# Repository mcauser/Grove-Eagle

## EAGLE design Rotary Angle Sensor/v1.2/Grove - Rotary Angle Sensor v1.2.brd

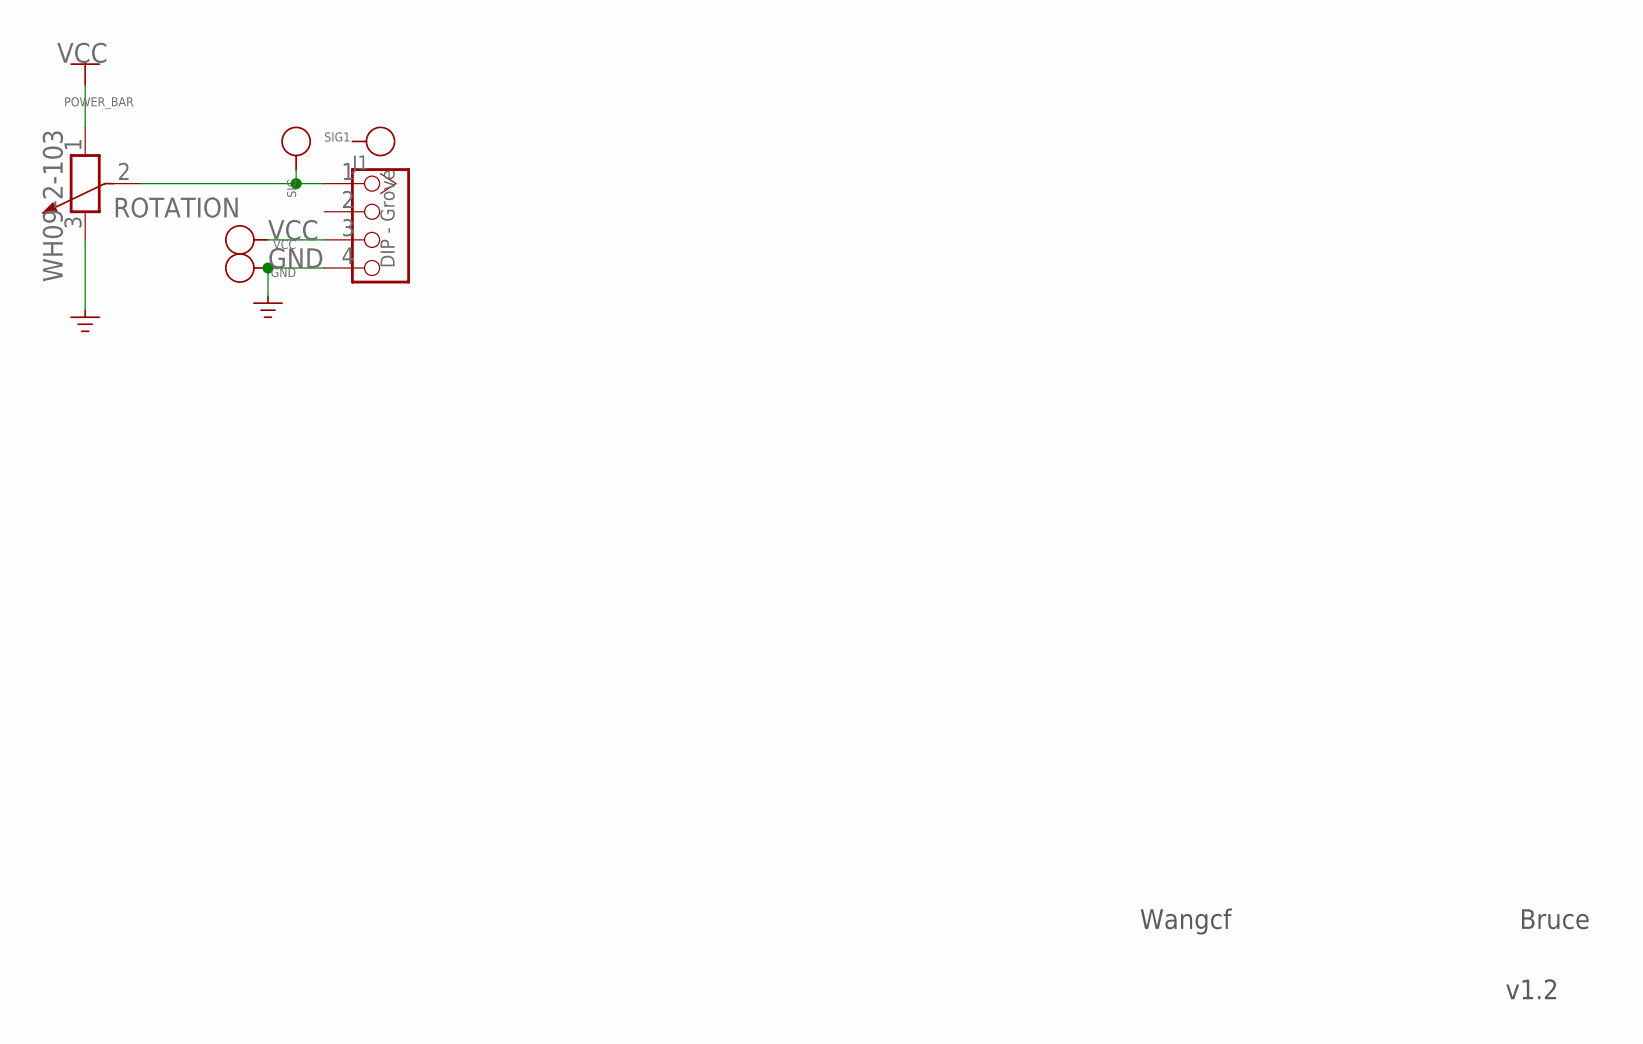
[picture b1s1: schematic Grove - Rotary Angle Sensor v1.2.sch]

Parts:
GND: PAD-TEST-POINT'4545'; TP_4545
J1: DIP - Grove; 4P-2.0
ROTATION: WH09-2-103; 3P-SQUA-11X9.8X12H
SIG, SIG1: PAD-TEST-POINT'4545'; TP_4545
VCC: PAD-TEST-POINT'4545'; TP_4545

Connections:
GND: GND.T, J1.4, ROTATION.3 (2)
unnamed: J1.1, ROTATION.2 (3), SIG.T
VCC: J1.3, ROTATION.1, VCC.T

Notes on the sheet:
Wangcf
Bruce
v1.2

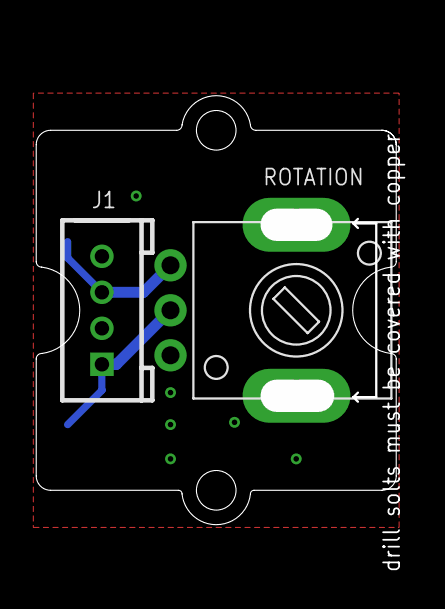
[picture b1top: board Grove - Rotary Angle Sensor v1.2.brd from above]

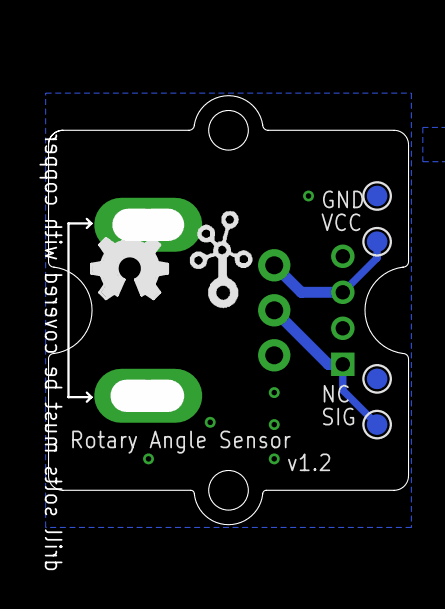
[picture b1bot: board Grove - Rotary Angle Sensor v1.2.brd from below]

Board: 2 copper layers, 20.0 x 23.8 mm, 9 parts (6 on the bottom side), 3 nets.

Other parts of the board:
U$5: 1U-DIM-W/-DRILL
U$6: OSHW_FILLX150_NOTEXT
U$9: TWIGLOGO_SMALL

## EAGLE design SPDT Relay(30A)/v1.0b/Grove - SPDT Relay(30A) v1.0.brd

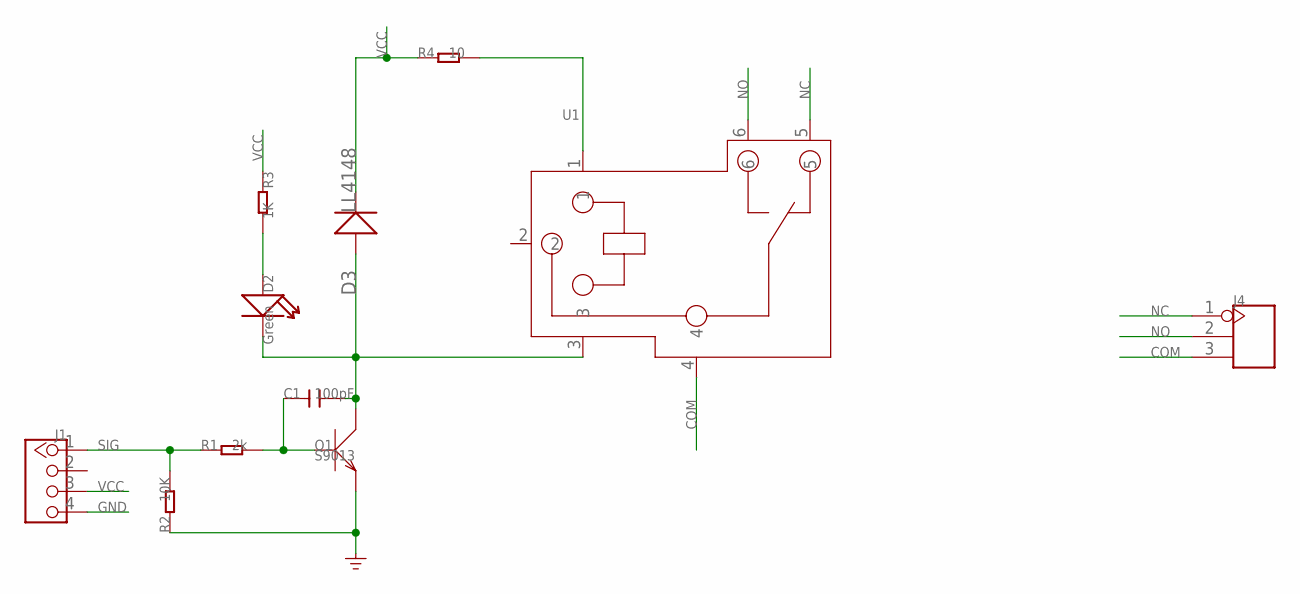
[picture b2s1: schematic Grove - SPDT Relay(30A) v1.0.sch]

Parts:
C1: 100pF; C0603
D2: Green; LED-0603
D3: LL4148; DO-35-SMD
J1: TWIG-4P-2.0-2.0; 4P-2.0
J4: SCREW-TERMINAL-3P'5.08'; 3P-5.08
Q1: S9013; SOT23
R1: 2k; R0603
R2: 10K; R0603
R3: 1K; R0603
R4: 10; R0603
U1: RELAY-SLA-05VDC-SL-C; 6P-19.8H

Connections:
COM: J4.3, U1.4
GND: J1.4, Q1.2 (E), R2.1
unnamed: C1.1, Q1.1 (B), R1.2
unnamed: D2.+, R3.2
unnamed: C1.2, D2.-, D3.A (+), Q1.3 (C), U1.3
unnamed: R4.2, U1.1
NC: J4.1, U1.5
NO: J4.2, U1.6
SIG: J1.1, R1.1, R2.2
VCC: D3.C (-), J1.3, R3.1, R4.1

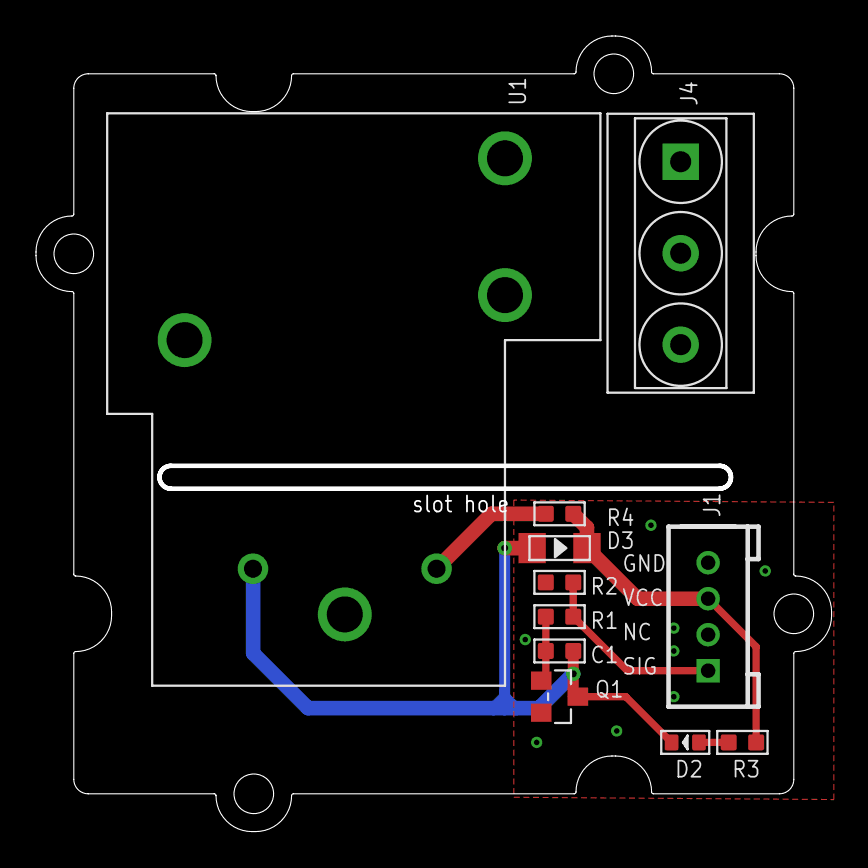
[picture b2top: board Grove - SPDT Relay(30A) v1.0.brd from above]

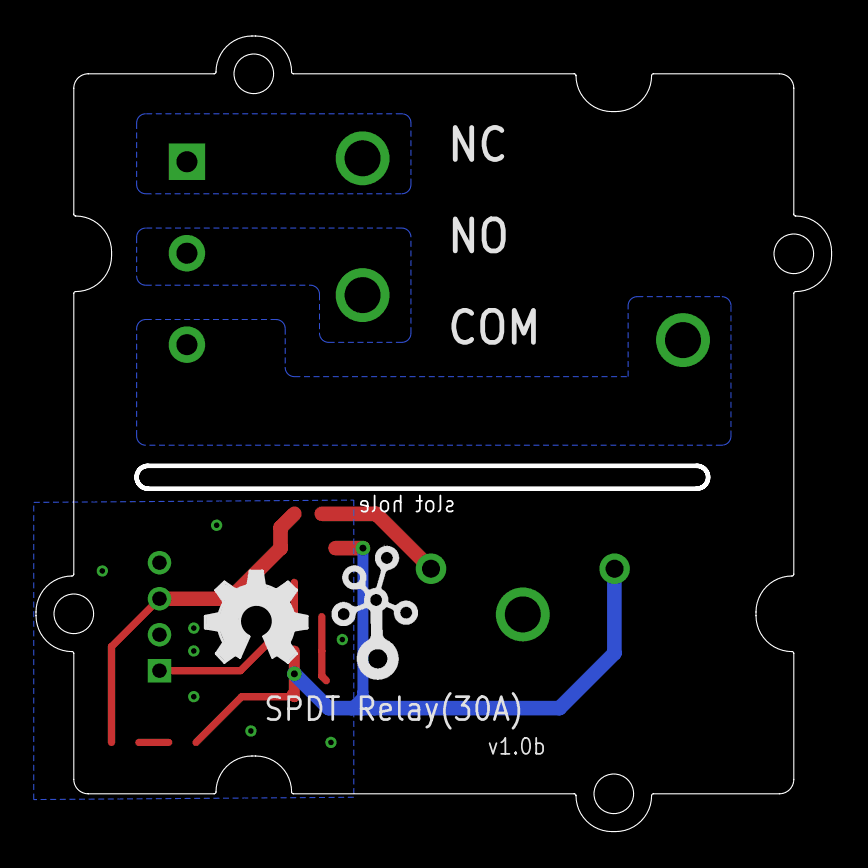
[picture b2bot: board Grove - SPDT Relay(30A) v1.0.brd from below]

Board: 2 copper layers, 44.2 x 44.2 mm, 14 parts (2 on the bottom side), 10 nets.

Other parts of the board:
U$3: 2X2U-DIM-W/-DRILL
U$4: OSHW_FILLX200_NOTEXT
U$5: TWIGLOGO

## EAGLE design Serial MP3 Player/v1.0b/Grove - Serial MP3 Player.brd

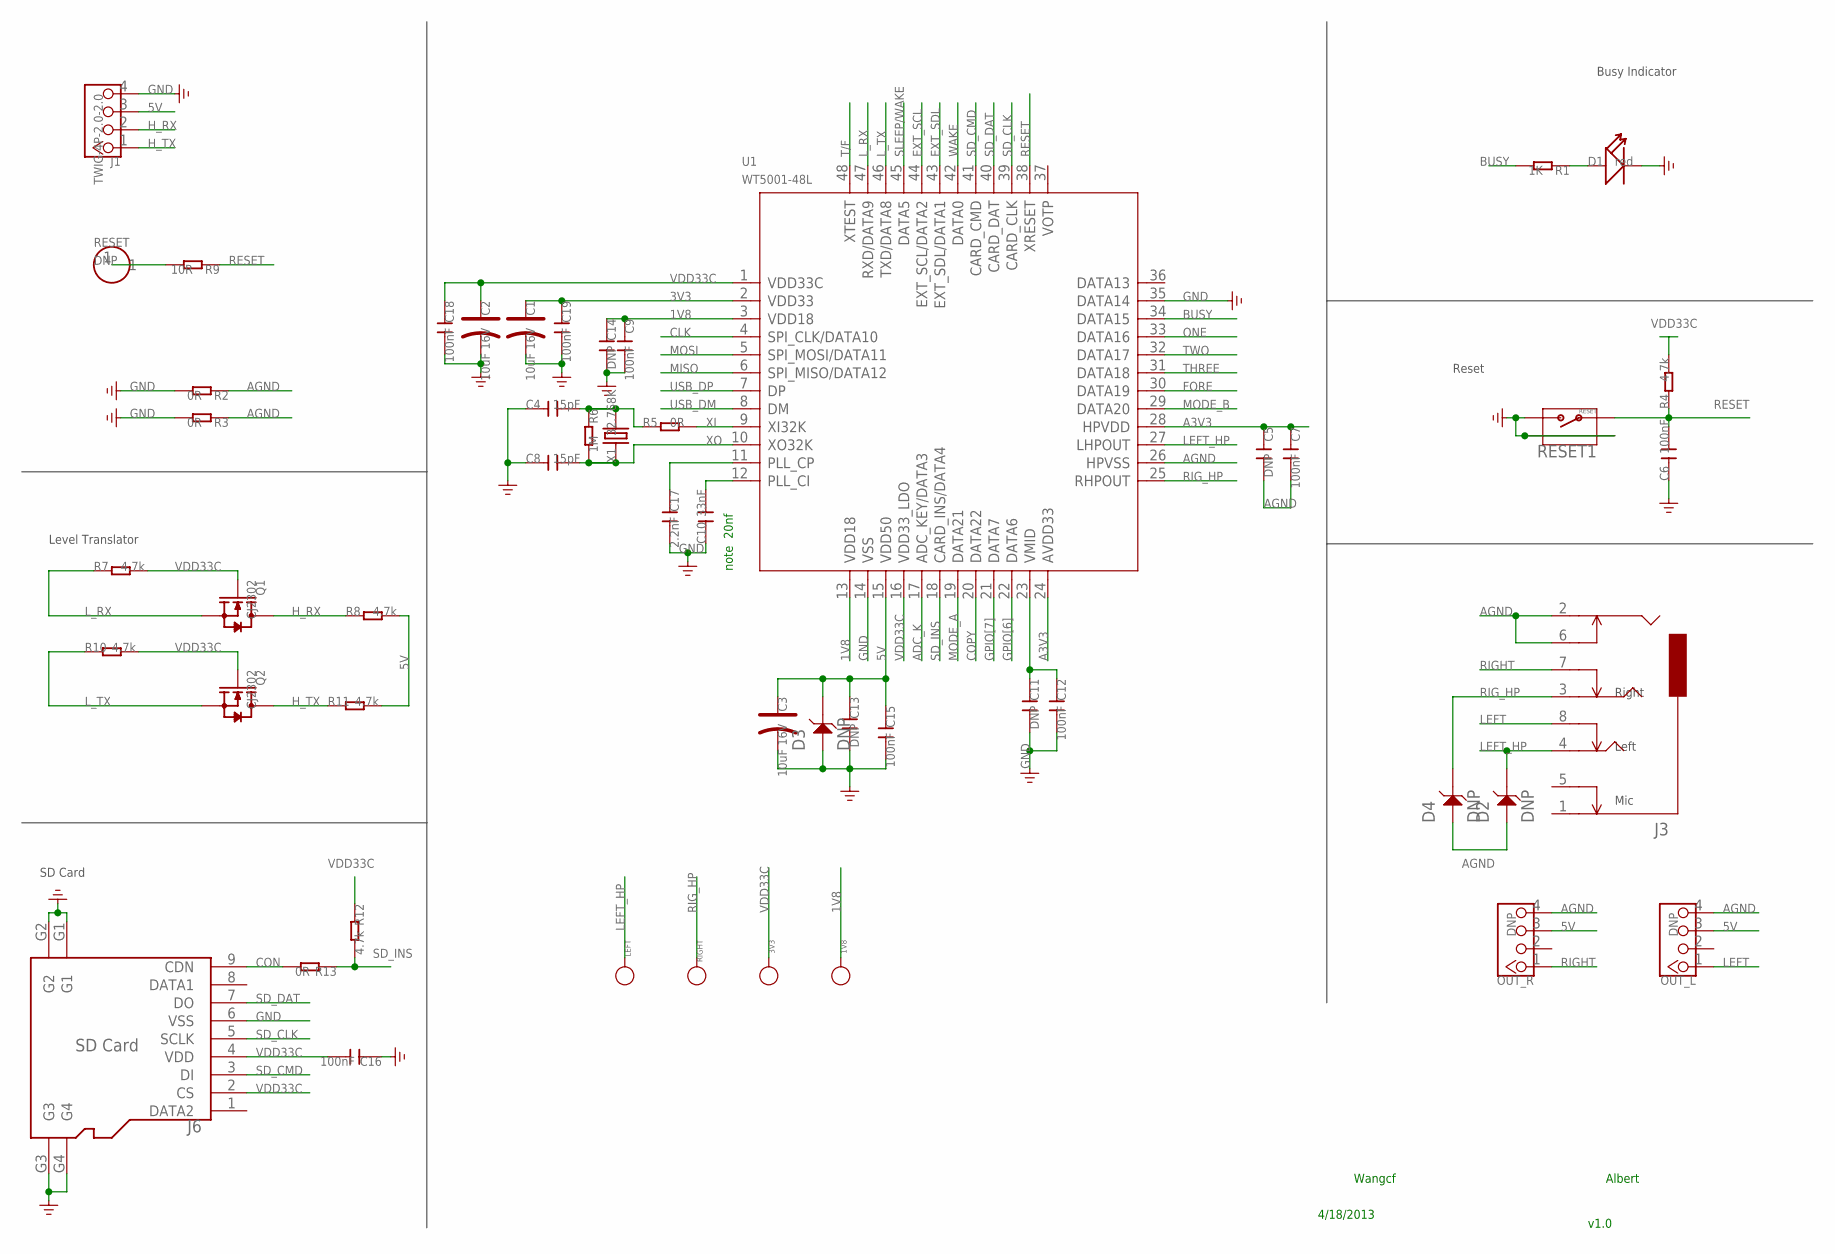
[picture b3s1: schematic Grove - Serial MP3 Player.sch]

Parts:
1V8, 3V3: PAD-TEST-POINT'4545'; TP_4545
C1, C2, C3: 10uF 16V; AVX-A
C4, C8: 15pF; C0603
C5, C11, C13, C14: DNP; C0805
C6, C7, C9, C12, C15, C16, C18, C19: 100nF; C0603
C10: 33nF; C0603
C17: 2.2nF; C0603
D1: red; LED-0603
D2, D3, D4: DNP; SOD123-2.7X1.6
J1: TWIG-4P-2.0-2.0; 4P-2.0
J3: AUDIO-8P-SMD'PJ-3536-L6S'; 8P-3.5-SMD
J6: SD Card; 9P-SMD-W/-RING
LEFT: PAD-TEST-POINT'4545'; TP_4545
OUT_L: DNP; 4P-2.0
OUT_R: DNP; 4P-2.0
Q1, Q2: CJ2302; SOT23
R1: 1K; R0603
R2, R3, R5, R13: 0R; R0603
R4, R7, R8, R10, R11, R12: 4.7k; R0603
R6: 1M; R0603
R9: 10R; R0603
RESET: DNP; 1P-65/35MIL
RESET1: RESET; 4P-SMD-7X3.5X3.5H
RIGHT: PAD-TEST-POINT'4545'; TP_4545
U1: WT5001-48L; TQFP48
X1: 32.768K; 2P-SMD-3.2X1.5

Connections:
1V8: 1V8.T, C9.1, C14.1, U1.3 (VDD18), U1.13 (VDD18)
3V3: C1.+, C19.1, U1.2 (VDD33)
5V: C3.+, C13.1, C15.1, D3.2, J1.3, OUT_L.3, OUT_R.3, R8.2, R11.2, U1.15 (VDD50)
A3V3: C5.1, C7.1, U1.24 (AVDD33), U1.28 (HPVDD)
ADC_K: U1.17 (ADC_KEY/DATA3)
AGND: C5.2, C7.2, D2.1, D4.1, J3.2, J3.6, OUT_L.4, OUT_R.4, R2.1, R3.1, U1.26 (HPVSS)
BUSY: R1.2, U1.34 (DATA15)
CLK: U1.4 (SPI_CLK/DATA10)
CON: J6.9 (CDN), R13.2
COPY: U1.20 (DATA22)
EXT_SCL: U1.44 (EXT_SCL/DATA2)
EXT_SDL: U1.43 (EXT_SDL/DATA1)
FORE: U1.30 (DATA19)
GND: C1.-, C2.-, C3.-, C4.1, C6.1, C8.1, C9.2, C10.1, C11.2, C12.2, C13.2, C14.2, C15.2, C16.1, C17.2, C18.2, C19.2, D1.-, D3.1, J1.4, J6.6 (VSS), J6.G1, J6.G2, J6.G3, J6.G4, R2.2, R3.2, RESET1.2, RESET1.S1, RESET1.S2, U1.14 (VSS), U1.35 (DATA14)
GPIO[6]: U1.22 (DATA6)
GPIO[7]: U1.21 (DATA7)
H_RX: J1.2, Q1.3 (D), R8.1
H_TX: J1.1, Q2.3 (D), R11.1
LEFT: J3.8, OUT_L.1
LEFT_HP: D2.2, J3.4, LEFT.T, U1.27 (LHPOUT)
LL: C4.2, R5.1, R6.1, X1.2
L_RX: Q1.2 (S), R7.1, U1.47 (RXD/DATA9)
L_TX: Q2.2 (S), R10.1, U1.46 (TXD/DATA8)
MISO: U1.6 (SPI_MISO/DATA12)
MODE_A: U1.19 (DATA21)
MODE_B: U1.29 (DATA20)
MOSI: U1.5 (SPI_MOSI/DATA11)
unnamed: C17.1, U1.11 (PLL_CP)
unnamed: C10.2, U1.12 (PLL_CI)
unnamed: C11.1, C12.1, U1.23 (VMID)
unnamed: R9.2, RESET.1
unnamed: D1.+, R1.1
ONE: U1.33 (DATA16)
RESET: C6.2, R4.1, R9.1, RESET1.1, U1.38 (XRESET)
RIGHT: J3.7, OUT_R.1
RIG_HP: D4.2, J3.3, RIGHT.T, U1.25 (RHPOUT)
SD_CLK: J6.5 (SCLK), U1.39 (CARD_CLK)
SD_CMD: J6.3 (DI), U1.41 (CARD_CMD)
SD_DAT: J6.7 (DO), U1.40 (CARD_DAT)
SD_INS: R12.2, R13.1, U1.18 (CARD_INS/DATA4)
SLEEP/WAKE: U1.45 (DATA5)
T/F: U1.48 (XTEST)
THREE: U1.31 (DATA18)
TWO: U1.32 (DATA17)
USB_DM: U1.8 (DM)
USB_DP: U1.7 (DP)
VDD33C: 3V3.T, C2.+, C16.2, C18.1, J6.2 (CS), J6.4 (VDD), Q1.1 (G), Q2.1 (G), R4.2, R7.2, R10.2, R12.1, U1.1 (VDD33C), U1.16 (VDD33_LDO)
WAKE: U1.42 (DATA0)
XI: R5.2, U1.9 (XI32K)
XO: C8.2, R6.2, U1.10 (XO32K), X1.1

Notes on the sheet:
Right
Left
Mic
SD Card
Level Translator
Busy Indicator
Reset
note 20nf
Wangcf
Albert
4/18/2013
v1.0

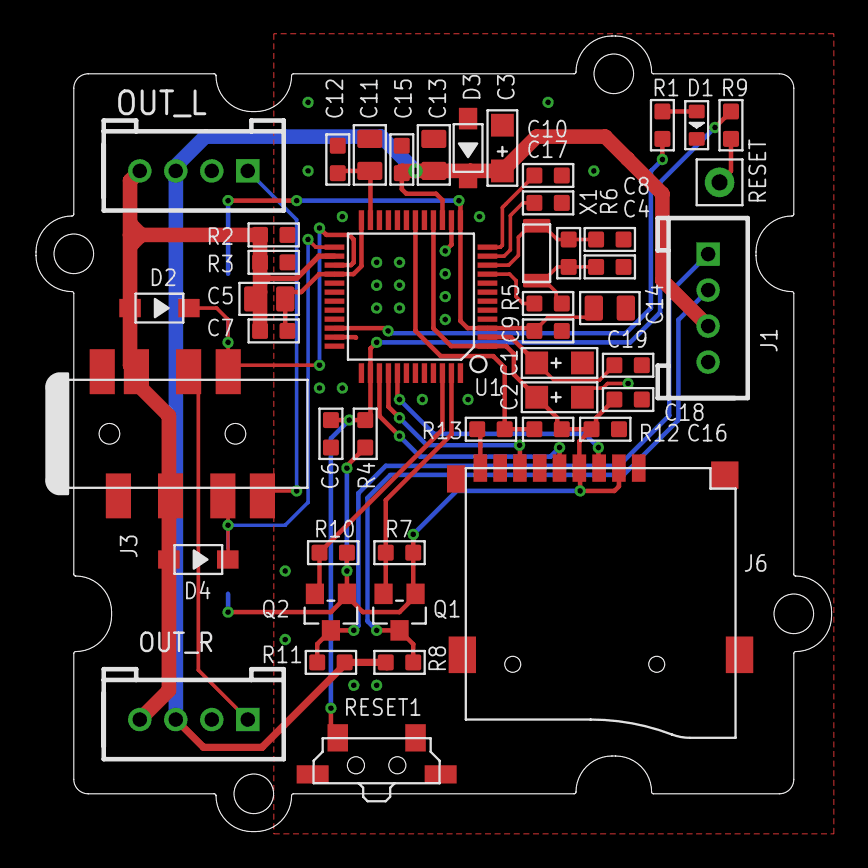
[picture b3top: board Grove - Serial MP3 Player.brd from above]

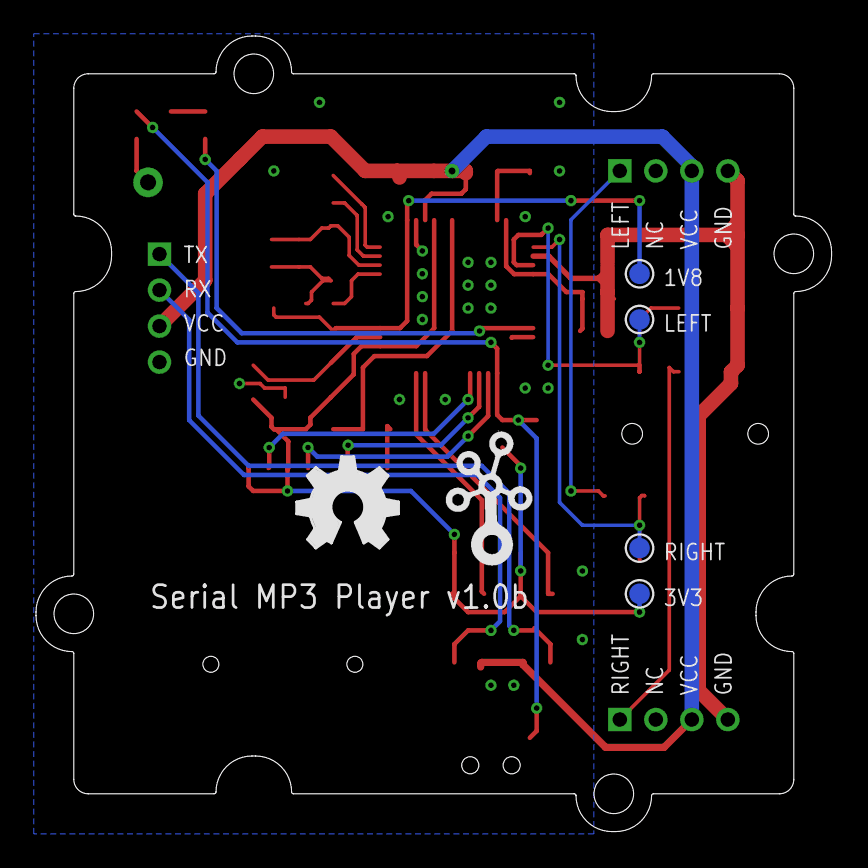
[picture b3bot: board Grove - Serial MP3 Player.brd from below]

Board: 2 copper layers, 44.2 x 44.2 mm, 54 parts (6 on the bottom side), 30 nets.

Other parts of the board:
U$13: TWIGLOGO
U$20: 2X2U-DIM-W/-DRILL
U$21: OSHW_FILLX200_NOTEXT

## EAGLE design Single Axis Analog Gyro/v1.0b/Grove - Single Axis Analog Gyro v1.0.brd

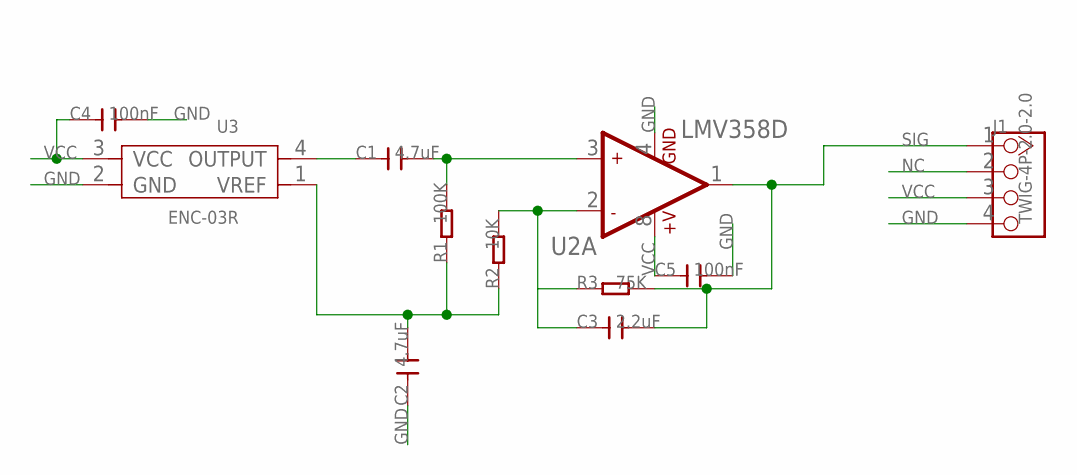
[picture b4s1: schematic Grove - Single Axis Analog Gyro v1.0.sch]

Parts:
C1, C2: 4.7uF; C0805
C3: 2.2uF; C0805
C4, C5: 100nF; C0603
J1: TWIG-4P-2.0-2.0; 4P-2.0
R1: 100K; R0603
R2: 10K; R0603
R3: 75K; R0603
U2: LMV358D; SO08
U3: ENC-03R; 4P-SMD-8X4X2H

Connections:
GND: C2.1, C4.2, C5.2, J1.4, U2.4 (GND), U3.2 (GND)
unnamed: C1.1, U3.4 (OUTPUT)
unnamed: C1.2, R1.2, U2.3 (+IN1)
unnamed: C2.2, R1.1, R2.1, U3.1 (VREF)
unnamed: C3.1, R2.2, R3.1, U2.2 (-IN1)
NC: J1.2
SIG: C3.2, J1.1, R3.2, U2.1 (OUT1)
VCC: C4.1, C5.1, J1.3, U2.8 (+V), U3.3 (VCC)

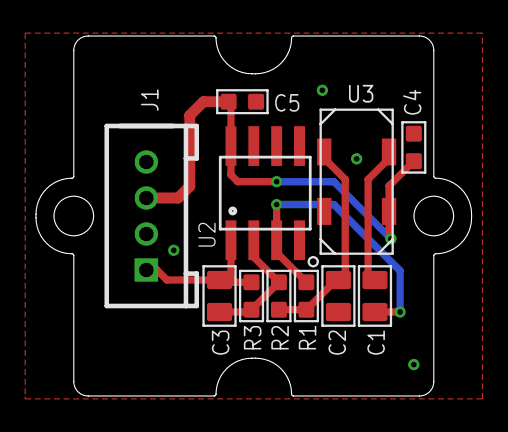
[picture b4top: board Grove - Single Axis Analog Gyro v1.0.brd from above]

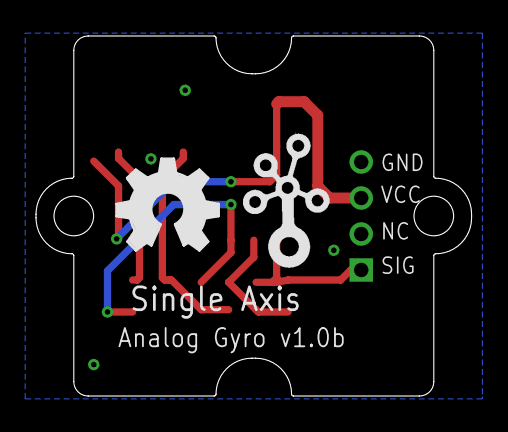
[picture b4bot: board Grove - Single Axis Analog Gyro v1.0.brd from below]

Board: 2 copper layers, 24.2 x 20.0 mm, 14 parts (2 on the bottom side), 7 nets.

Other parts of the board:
U$1: 1U-DIM-W/-DRILL
U$2: OSHW_FILLX200_NOTEXT
U$3: TWIGLOGO
